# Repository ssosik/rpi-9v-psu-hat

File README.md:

# Raspberry Pi Preamp PSU HAT — Rev 4

A KiCad-designed Raspberry Pi HAT that generates a clean, isolated +9V supply from the Pi's 5V GPIO rail, intended to power low-noise electret microphone preamplifier circuits (such as the [ESP P93](https://sound-au.com/project93.htm)) for field audio recording applications like [BirdNET-Pi](https://github.com/mcguirepr89/BirdNET-Pi).

## Schematic

## PCB Layout

## Overview

The Pi's 5V supply rail is noisy — unsuitable for sensitive microphone preamp circuits without significant filtering and regulation. This HAT addresses that with a multi-stage power supply chain:

1. **Stage 1 — Input filter**: Ferrite bead + 4.7Ω series resistor + capacitors (100µF + 1µF) attenuate high-frequency noise on the 5V input and limit inrush from the Pi
2. **Isolated DC-DC conversion**: NMH0515SC converts 5V to ±15V with galvanic isolation, breaking any ground-loop path between the Pi and the preamp
3. **LC filter**: 100µH inductor + capacitors (10µF + 4.7µF + 100nF) reduce switching noise from the DC-DC converter
4. **Linear regulation**: MC7809CTG drops the rectified +15V to a clean, regulated +9V
5. **Stage 2 — Output filter**: 47Ω series resistor + capacitor bank (100µF + 100nF) + ferrite bead attenuates residual ripple before the output connectors

The filtered +9V is available on two paralleled outputs: **OUT1**, a JST XH 2-pin header, and **OUT2**, a 2.1mm DC barrel jack (**center-positive**, marked `CTR+` on the silkscreen).

## Key Components

| Designator | Part | Description |
|---|---|---|
| U1 | NMH0515SC | 5V → ±15V isolated DC-DC converter (Murata) |
| U2 | MC7809CTG | +9V linear regulator, TO-220 |
| L1 | 11R104C | 100µH radial inductor |
| FB1, FB2 | e.g. Murata BLM21AG601 | 0805 ferrite beads, ~600Ω @ 100MHz |
| J1 | 2×20 pin socket | Raspberry Pi GPIO header |
| OUT1 | JST XH B2B-XH-A | +9V filtered output, 2-pin |
| OUT2 | CUI PJ-102AH | +9V filtered output, 2.1mm barrel jack, center-positive |
| MH1, MH2 | M2.5 NPTH | Mounting holes on the Pi HAT hole pattern |

Full bill of materials: [`rpi-preamp-psu-hat-BoM.csv`](rpi-preamp-psu-hat-BoM.csv)

## Usage

### Hardware stack

```
[Raspberry Pi 4B]
      ↓ GPIO (5V + GND)
[This PSU HAT]
      ↓ JST XH or 2.1mm barrel (filtered +9V)
[P93 Stereo Preamp board]  ← electret capsules (EM272 or similar)
      ↓ balanced XLR
[HiFiBerry DAC+ ADC Pro]
      ↓ GPIO
[Raspberry Pi 4B]
```

### Stacking height

The HAT uses tall through-hole electrolytics (C_9V1, C_REG1: 100µF/16V, 8mm body). When stacking additional HATs, use an extra-tall stacking header to clear the tallest capacitors:

- **10mm stacking header** — [Adafruit #2223](https://www.adafruit.com/product/2223) (minimum clearance)
- **23mm stacking header** — [Adafruit #1979](https://www.adafruit.com/product/1979) (recommended)

Add M2.5 standoffs at the two mounting holes (MH1, MH2). They sit on the standard Pi HAT hole pattern beside the GPIO header.

## Design notes

A few non-obvious conventions to keep in mind before modifying the schematic or PCB:

### Grounding

There are **two distinct ground nets**: `Pi_GND` (everything upstream of U1) and `ISO_GND` (everything downstream of U1). Galvanic isolation across the NMH0515SC is the whole point of this board — bridging the two grounds anywhere (in the schematic, in PCB copper, or via mounting hardware) defeats the design. On the PCB, each domain has its own pour on both copper layers, with a 2.54mm copper-free channel between them. The mounting holes are non-plated with no copper land, so they are not connected to either ground. Keep it that way: a plated hole bonded to `Pi_GND` would let a metal standoff carry Pi ground into the case.

### Why R_BLEED1 exists

The NMH0515SC produces ±15V but only the +15V rail feeds the 7809 — the −15V rail is otherwise unloaded. `R_BLEED1` (1k5 across −15V → ISO_GND, ≈10mA ≈ 15% of rated load) provides minimum load on the unused rail so the converter's cross-regulation keeps the +15V rail stable. It is not optional; do not "clean it up."

### Output voltage under load

R_9V1 (47Ω) is in series with the load, so the output sits below 9V: at ~20mA (two preamp channels) the drop is ~0.94V, giving ~8V at OUT1/OUT2. This is intentional. The 47Ω is what sets the Stage 2 RC corner (~34Hz with C_9V1), and the P93 preamp is happy at 8V.

### Net naming

Suffixes on the rail names carry meaning:

| Net | Meaning |
|---|---|
| `+15V` | Raw output of U1 |
| `+15V_f` | Post-LC-filter, going into U2's input pin |
| `+9V` | Raw 7809 output |
| `+9V_filt` | After R_9V1 (Stage 2 RC node: C_9V1, C_9V2) |
| `+9V_filt_out` | After FB2, at the output connectors OUT1 / OUT2 |

When tracing the schematic, the `_f` / `_filt` suffix tells you which side of a filter stage a net is on.

### Reference designators

This project uses **descriptive refdes** (`C_NMH1`, `C_REG2`, `R_BLEED1`, `R_9V1`) rather than sequential `C1, C2, R1`. The prefix names the stage or role:

- `IN*` — Stage 1 input filter
- `NMH*` — around U1 (NMH0515SC)
- `REG*` — around U2 (the 7809 regulator)
- `9V*` — Stage 2 output filter
- `BLEED*` — the −15V bleeder

KiCad's auto-annotation will destroy these names — don't run it without intent.

### Custom footprint library

`stereo-preamp-psu.pretty/` is a project-local footprint library (registered in `fp-lib-table` via `${KIPRJMOD}`). It contains:

- `CP_Radial_D5.0mm_P5.00mm`: used by `C_NMH1`
- `Logo_sosik_7.5mm`: front-silkscreen logo, generated from `logo.kicad_sym`

Keep the directory alongside the project files. Deleting it breaks those footprint references.

## Files

| File | Description |
|---|---|
| `rpi-preamp-psu-hat.kicad_sch` | KiCad schematic |
| `rpi-preamp-psu-hat.kicad_pcb` | KiCad PCB layout |
| `rpi-preamp-psu-hat.kicad_pro` | KiCad project file |
| `rpi-preamp-psu-hat-BoM.csv` | Bill of materials |
| `rpi-preamp-psu-hat-erc.rpt` / `-drc.rpt` | Latest ERC / DRC reports |
| `logo.kicad_sym` | Logo artwork (bitmap2component output), source for the logo footprint |
| `PLAN.md` | Design-review log and open items |
| `gerbers/` | Gerber files ready for fab |
| `gerbers.zip` | Gerber zip for direct upload to PCB fab |

## Fabrication Notes

- Board is designed for standard 2-layer FR4, 1.6mm
- Through-hole parts on top; FB1/FB2 are the only SMD parts (0805, hand-solderable)
- Component reference/value silkscreen text is 0.6mm tall to fit the layout. That is below KiCad's default 0.8mm minimum, so DRC raises warnings. Confirm your fab's minimum before ordering

## License

Released under [CERN Open Hardware Licence v2 – Strongly Reciprocal (CERN-OHL-S)](https://ohwr.org/cern_ohl_s_v2.txt). Derivatives must be released under the same license with design files made available.

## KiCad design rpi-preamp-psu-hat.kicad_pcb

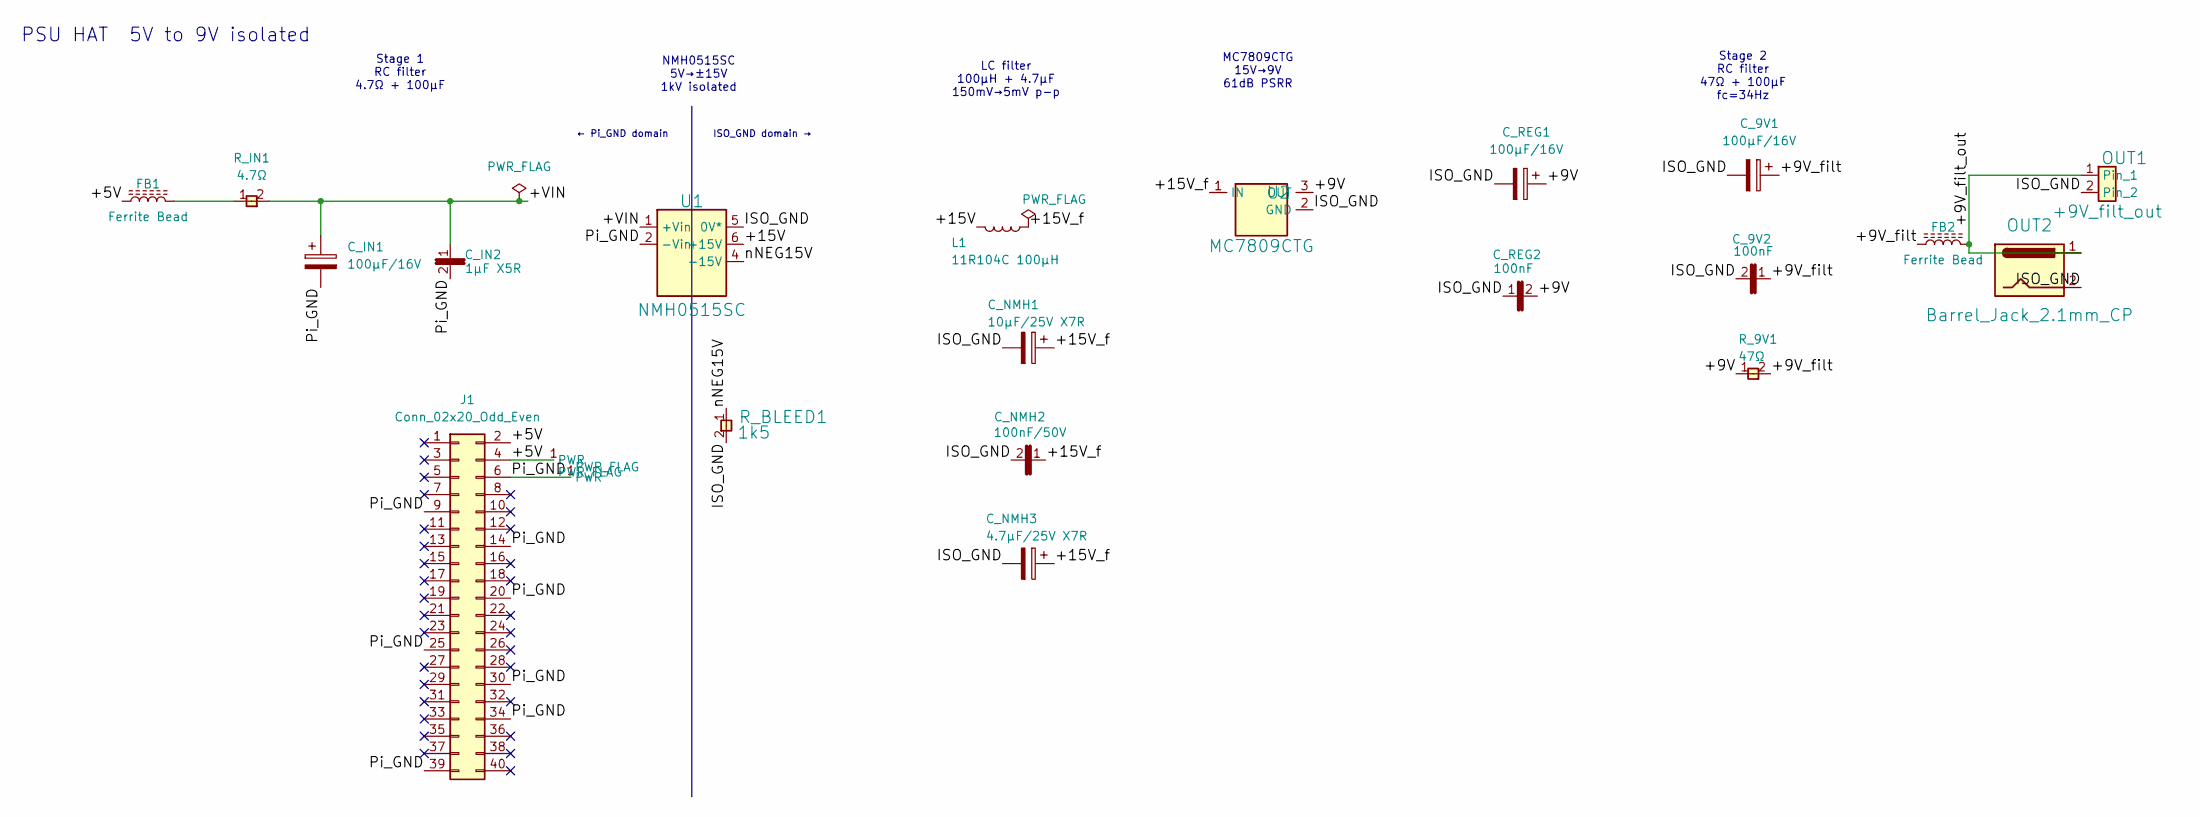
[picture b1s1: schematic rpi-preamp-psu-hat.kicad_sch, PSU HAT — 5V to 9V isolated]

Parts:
C_9V1: 100µF/16V; CP_Radial_D8.0mm_P5.00mm
C_9V2: 100nF; C_Disc_D5.0mm_W2.5mm_P2.50mm
C_IN1: 100µF/16V; CP_Radial_D8.0mm_P5.00mm
C_IN2: 1µF X5R; C_Disc_D5.0mm_W2.5mm_P5.00mm
C_NMH1: 10µF/25V X7R; CP_Radial_D5.0mm_P5.00mm
C_NMH2: 100nF/50V; C_Disc_D5.0mm_W2.5mm_P2.50mm
C_NMH3: 4.7µF/25V X7R; CP_Radial_D5.0mm_P2.50mm
C_REG1: 100µF/16V; CP_Radial_D8.0mm_P5.00mm
C_REG2: 100nF; C_Disc_D5.0mm_W2.5mm_P2.50mm
FB1, FB2: Ferrite Bead; L_0805_2012Metric_Pad1.05x1.20mm_HandSolder
J1: Conn_02x20_Odd_Even; PinSocket_2x20_P2.54mm_Vertical
L1: 11R104C 100µH; L_Radial_D5.0mm_H7.5mm_P2.00mm
OUT1: +9V_filt_out; JST_XH_B2B-XH-A_1x02_P2.50mm_Vertical
OUT2: Barrel_Jack_2.1mm_CP; BarrelJack_CUI_PJ-102AH_Horizontal
R_9V1: 47Ω; R_Axial_DIN0204_L3.6mm_D1.6mm_P2.54mm_Vertical
R_BLEED1: 1k5; R_Axial_DIN0204_L3.6mm_D1.6mm_P2.54mm_Vertical
R_IN1: 4.7Ω; R_Axial_DIN0204_L3.6mm_D1.6mm_P2.54mm_Vertical
U1: NMH0515SC; Converter_DCDC_Murata_NMAxxxxSC_THT
U2: MC7809CTG; TO-220-3_Vertical

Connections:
/+5V: FB1.1, J1.2, J1.4
/+9V: C_REG1.1, C_REG2.2, R_9V1.1, U2.3 (OUT)
/+9V_filt: C_9V1.1, C_9V2.1, FB2.1, R_9V1.2
/+9V_filt_out: FB2.2, OUT1.1, OUT2.1
/+15V: L1.2, U1.6 (+15V)
/+15V_f: C_NMH1.1, C_NMH2.1, C_NMH3.1, L1.1, U2.1 (IN)
/+VIN: C_IN1.1, C_IN2.1, R_IN1.2, U1.1 (+Vin)
/ISO_GND: C_9V1.2, C_9V2.2, C_NMH1.2, C_NMH2.2, C_NMH3.2, C_REG1.2, C_REG2.1, OUT1.2, OUT2.2, R_BLEED1.2, U1.5 (0V*), U2.2 (GND)
/Pi_GND: C_IN1.2, C_IN2.2, J1.6, J1.9, J1.14, J1.20, J1.25, J1.30, J1.34, J1.39, U1.2 (-Vin)
/nNEG15V: R_BLEED1.1, U1.4 (-15V)
unnamed: FB1.2, R_IN1.1

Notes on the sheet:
Stage 1 RC filter 4.7Ω + 100µF
MC7809CTG 15V→9V 61dB PSRR
NMH0515SC 5V→±15V 1kV isolated
ISO_GND domain →
PSU HAT 5V to 9V isolated
← Pi_GND domain
LC filter 100µH + 4.7µF 150mV→5mV p-p
Stage 2 RC filter 47Ω + 100µF fc=34Hz

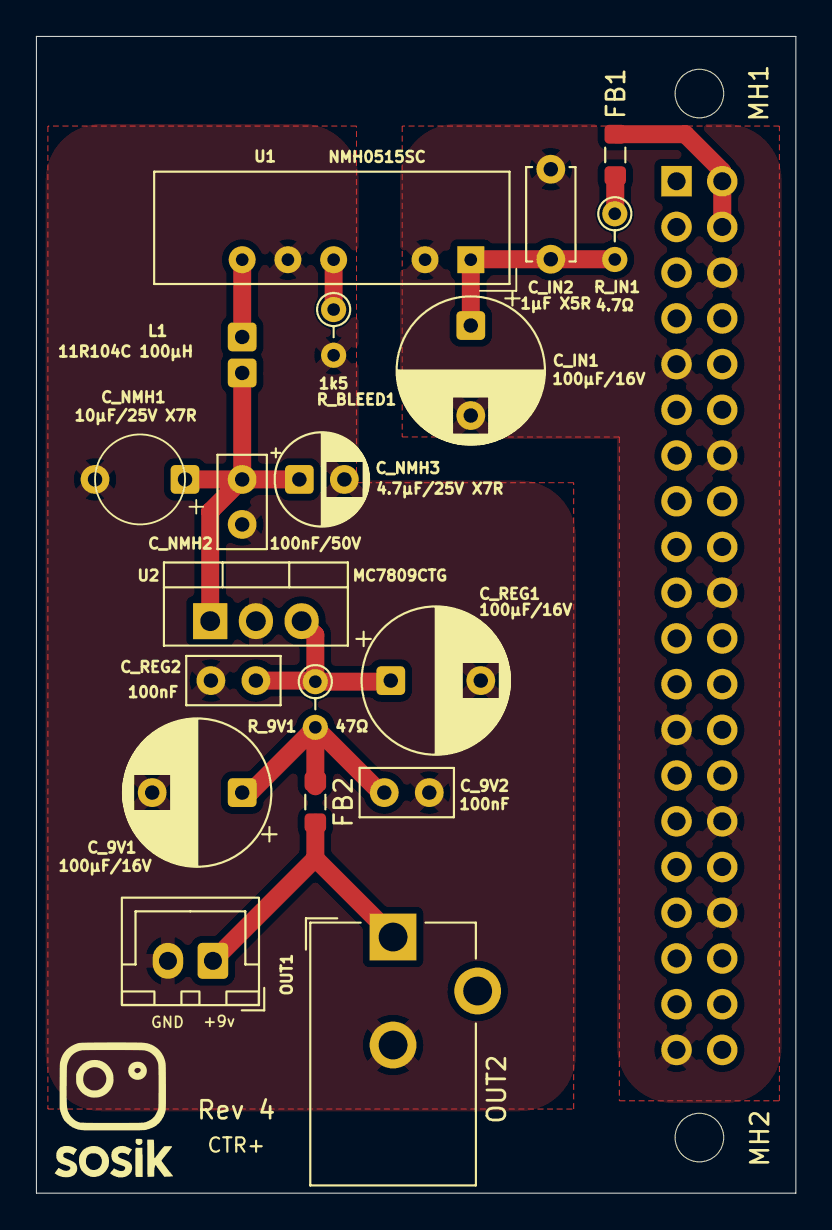
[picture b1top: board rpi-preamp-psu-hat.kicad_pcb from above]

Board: 2 copper layers, 42.2 x 64.3 mm, 23 parts (1 on the bottom side), 11 nets.

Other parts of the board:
LOGO1: Logo_sosik; Logo_sosik_7.5mm
MH1, MH2: MountingHole_2.7mm_M2.5_DIN965

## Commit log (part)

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2026-03-31 Ordered!
2026-03-31 Initial add, good starting point
2026-04-21 Cleanups for publishing
2026-04-26 Add README and a PCB tweaks
2026-06-13 Checkpoint
2026-06-16 chkp
2026-06-16 CHeck[oint
2026-06-17 chkpt
